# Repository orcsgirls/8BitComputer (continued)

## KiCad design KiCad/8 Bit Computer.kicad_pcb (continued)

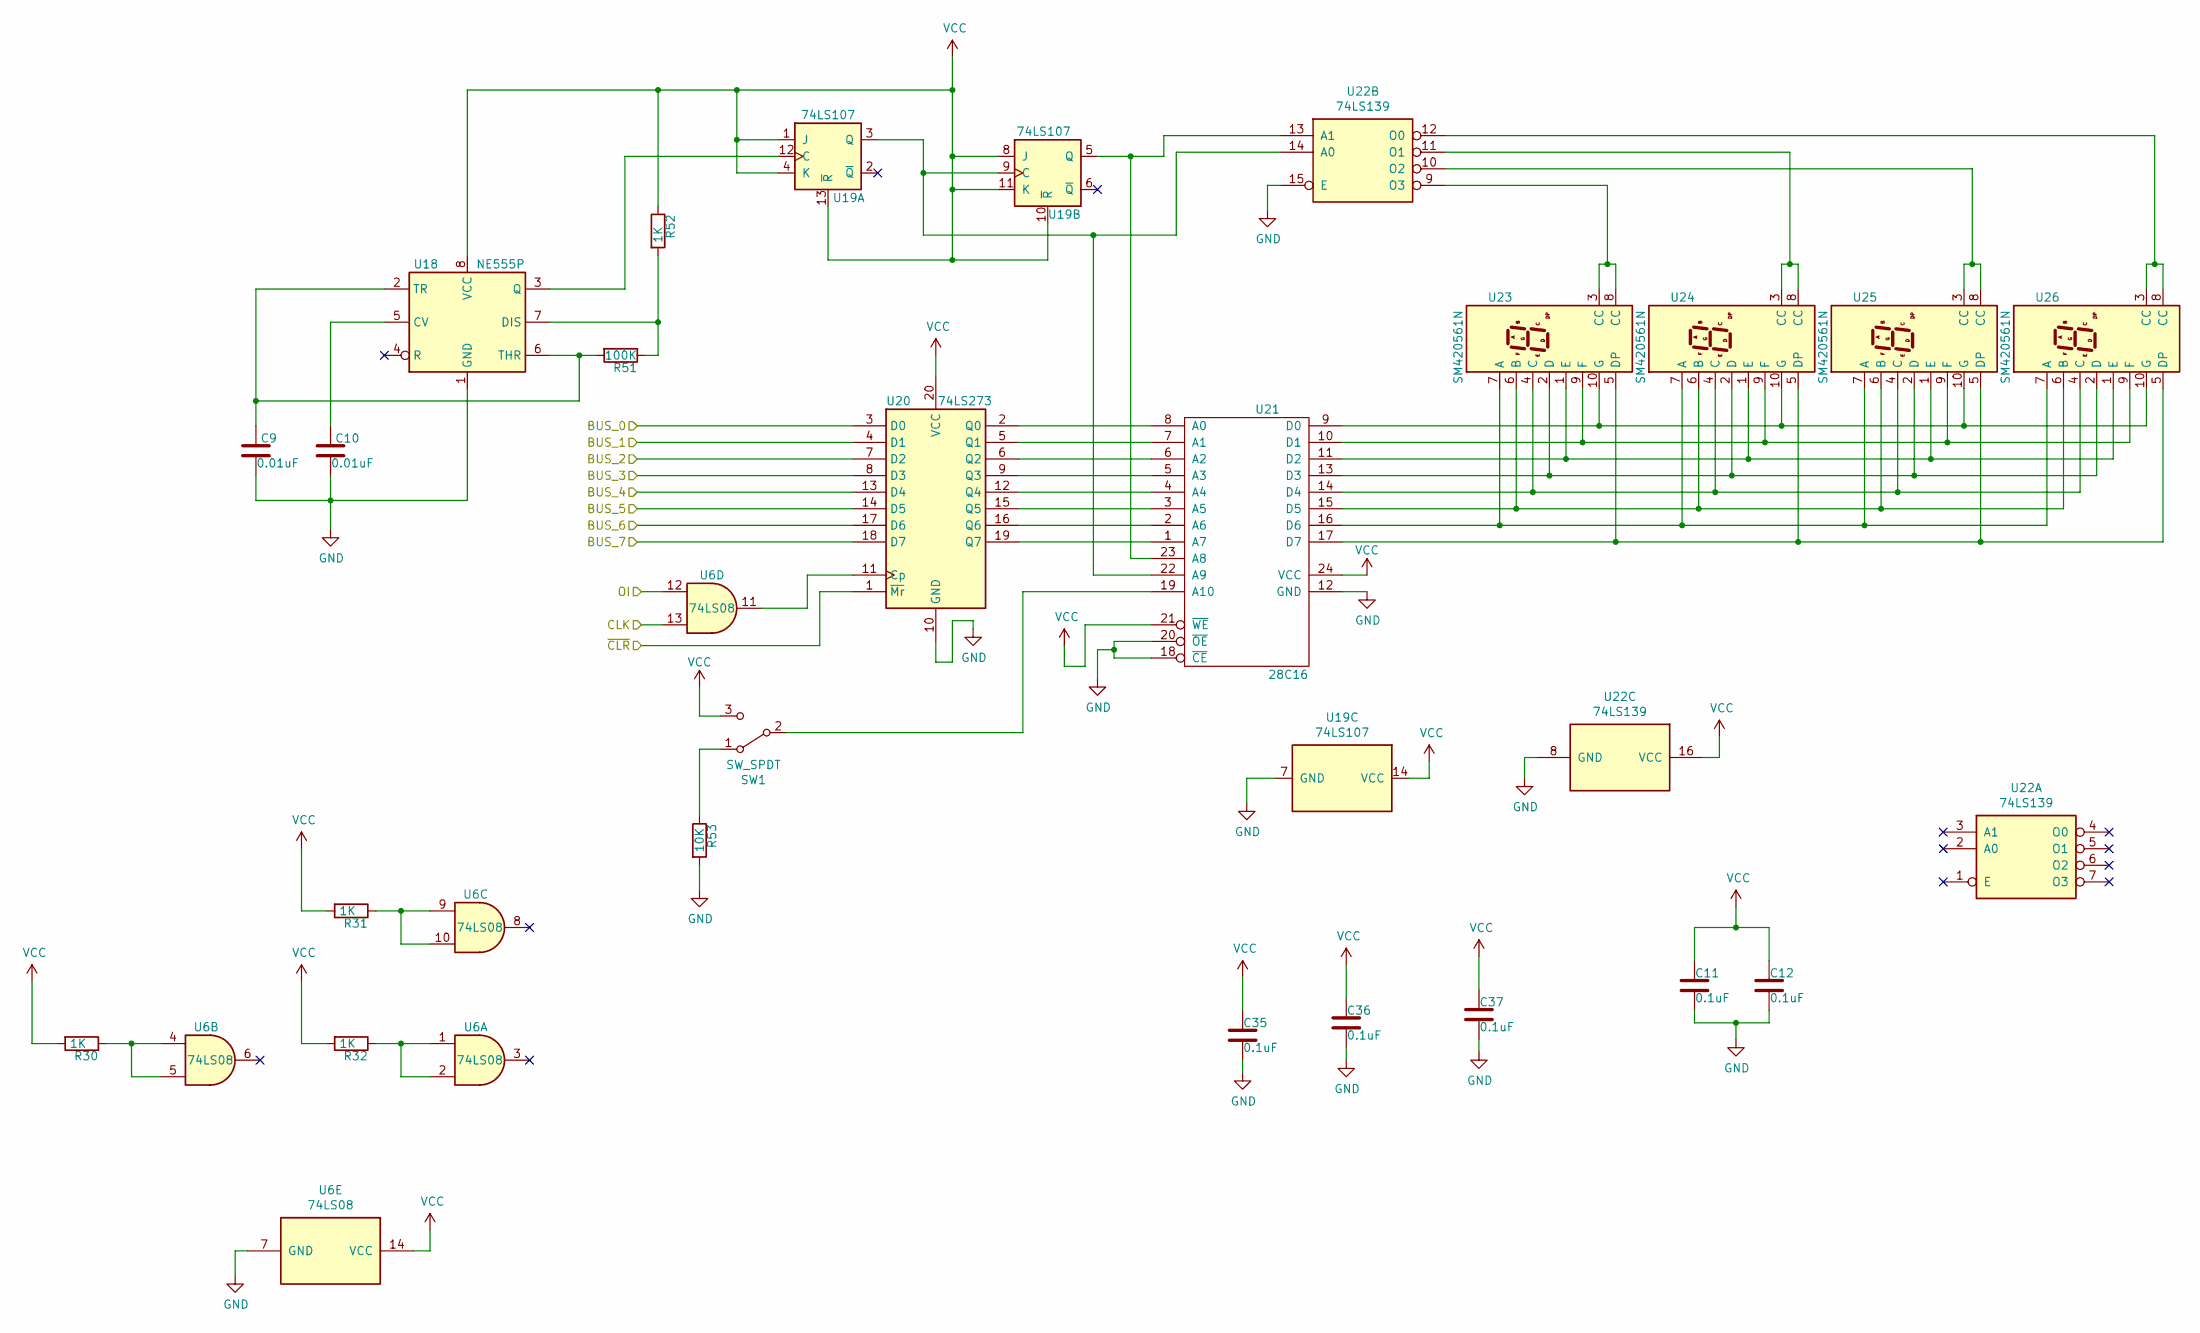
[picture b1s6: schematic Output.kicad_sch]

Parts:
C9, C10: 0.01uF; C_Disc_D4.3mm_W1.9mm_P5.00mm
C11, C12, C35, C36, C37: 0.1uF; C_Disc_D4.3mm_W1.9mm_P5.00mm
R30, R31, R32, R52: 1K; R_Axial_DIN0207_L6.3mm_D2.5mm_P7.62mm_Horizontal
R51: 100K; R_Axial_DIN0207_L6.3mm_D2.5mm_P7.62mm_Horizontal
R53: 10K; R_Axial_DIN0207_L6.3mm_D2.5mm_P7.62mm_Horizontal
SW1: SW_SPDT; SW_Slide_1P2T_CK_OS102011MS2Q
U6: 74LS08; DIP-14_W7.62mm_Socket_LongPads
U18: NE555P; DIP-8_W7.62mm_Socket_LongPads
U19: 74LS107; DIP-14_W7.62mm_Socket_LongPads
U20: 74LS273; DIP-20_W7.62mm_Socket_LongPads
U21: 28C16; DIP-24_W15.24mm_Socket_LongPads
U22: 74LS139; DIP-16_W7.62mm_Socket_LongPads
U23, U24, U25, U26: SM420561N; 7SegmentLED_LTS6760_LTS6780

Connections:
/ALU/BUS_0: U20.3 (D0); also elsewhere on the board
/ALU/BUS_1: U20.4 (D1); also elsewhere on the board
/ALU/BUS_2: U20.7 (D2); also elsewhere on the board
/ALU/BUS_3: U20.8 (D3); also elsewhere on the board
/ALU/BUS_4: U20.13 (D4); also elsewhere on the board
/ALU/BUS_5: U20.14 (D5); also elsewhere on the board
/ALU/BUS_6: U20.17 (D6); also elsewhere on the board
/ALU/BUS_7: U20.18 (D7); also elsewhere on the board
/ALU/CLK: U6.13; also elsewhere on the board
/Arduino_Interface/~CLR: U20.1 (~Mr); also elsewhere on the board
/Control_Logic/OI: U6.12; also elsewhere on the board
GND: C9.2, C10.2, C11.2, C12.2, C35.2, C36.2, C37.2, R53.2, U6.7 (GND), U18.1 (GND), U19.7 (GND), U20.10 (GND), U21.12 (GND), U21.18 (~CE), U21.20 (~OE), U22.8 (GND), U22.15 (E); also elsewhere on the board
unnamed: R30.1, U6.4, U6.5
unnamed: R31.1, U6.9, U6.10
unnamed: R32.1, U6.1, U6.2
unnamed: R53.1, SW1.1 (A)
unnamed: SW1.2 (B), U21.19 (A10)
unnamed: C10.1, U18.5 (CV)
unnamed: R51.1, R52.2, U18.7 (DIS)
unnamed: U18.3 (Q), U19.12 (C)
unnamed: C9.1, R51.2, U18.2 (TR), U18.6 (THR)
unnamed: U19.3 (Q), U19.9 (C), U21.22 (A9), U22.14 (A0)
unnamed: U19.5 (Q), U21.23 (A8), U22.13 (A1)
unnamed: U6.11, U20.11 (Cp)
unnamed: U20.2 (Q0), U21.8 (A0)
unnamed: U20.5 (Q1), U21.7 (A1)
unnamed: U20.6 (Q2), U21.6 (A2)
unnamed: U20.9 (Q3), U21.5 (A3)
unnamed: U20.12 (Q4), U21.4 (A4)
unnamed: U20.15 (Q5), U21.3 (A5)
unnamed: U20.16 (Q6), U21.2 (A6)
unnamed: U20.19 (Q7), U21.1 (A7)
unnamed: U21.9 (D0), U23.10 (G), U24.10 (G), U25.10 (G), U26.10 (G)
unnamed: U21.10 (D1), U23.9 (F), U24.9 (F), U25.9 (F), U26.9 (F)
unnamed: U21.11 (D2), U23.1 (E), U24.1 (E), U25.1 (E), U26.1 (E)
unnamed: U21.13 (D3), U23.2 (D), U24.2 (D), U25.2 (D), U26.2 (D)
unnamed: U21.14 (D4), U23.4 (C), U24.4 (C), U25.4 (C), U26.4 (C)
unnamed: U21.15 (D5), U23.6 (B), U24.6 (B), U25.6 (B), U26.6 (B)
unnamed: U21.16 (D6), U23.7 (A), U24.7 (A), U25.7 (A), U26.7 (A)
unnamed: U21.17 (D7), U23.5 (DP), U24.5 (DP), U25.5 (DP), U26.5 (DP)
unnamed: U22.12 (O0), U26.3 (CC), U26.8 (CC)
unnamed: U22.11 (O1), U24.3 (CC), U24.8 (CC)
unnamed: U22.10 (O2), U25.3 (CC), U25.8 (CC)
unnamed: U22.9 (O3), U23.3 (CC), U23.8 (CC)
VCC: C11.1, C12.1, C35.1, C36.1, C37.1, R30.2, R31.2, R32.2, R52.1, SW1.3 (C), U6.14 (VCC), U18.8 (VCC), U19.1 (J), U19.4 (K), U19.8 (J), U19.10 (~R), U19.11 (K), U19.13 (~R), U19.14 (VCC), U20.20 (VCC), U21.21 (~WE), U21.24 (VCC), U22.16 (VCC); also elsewhere on the board

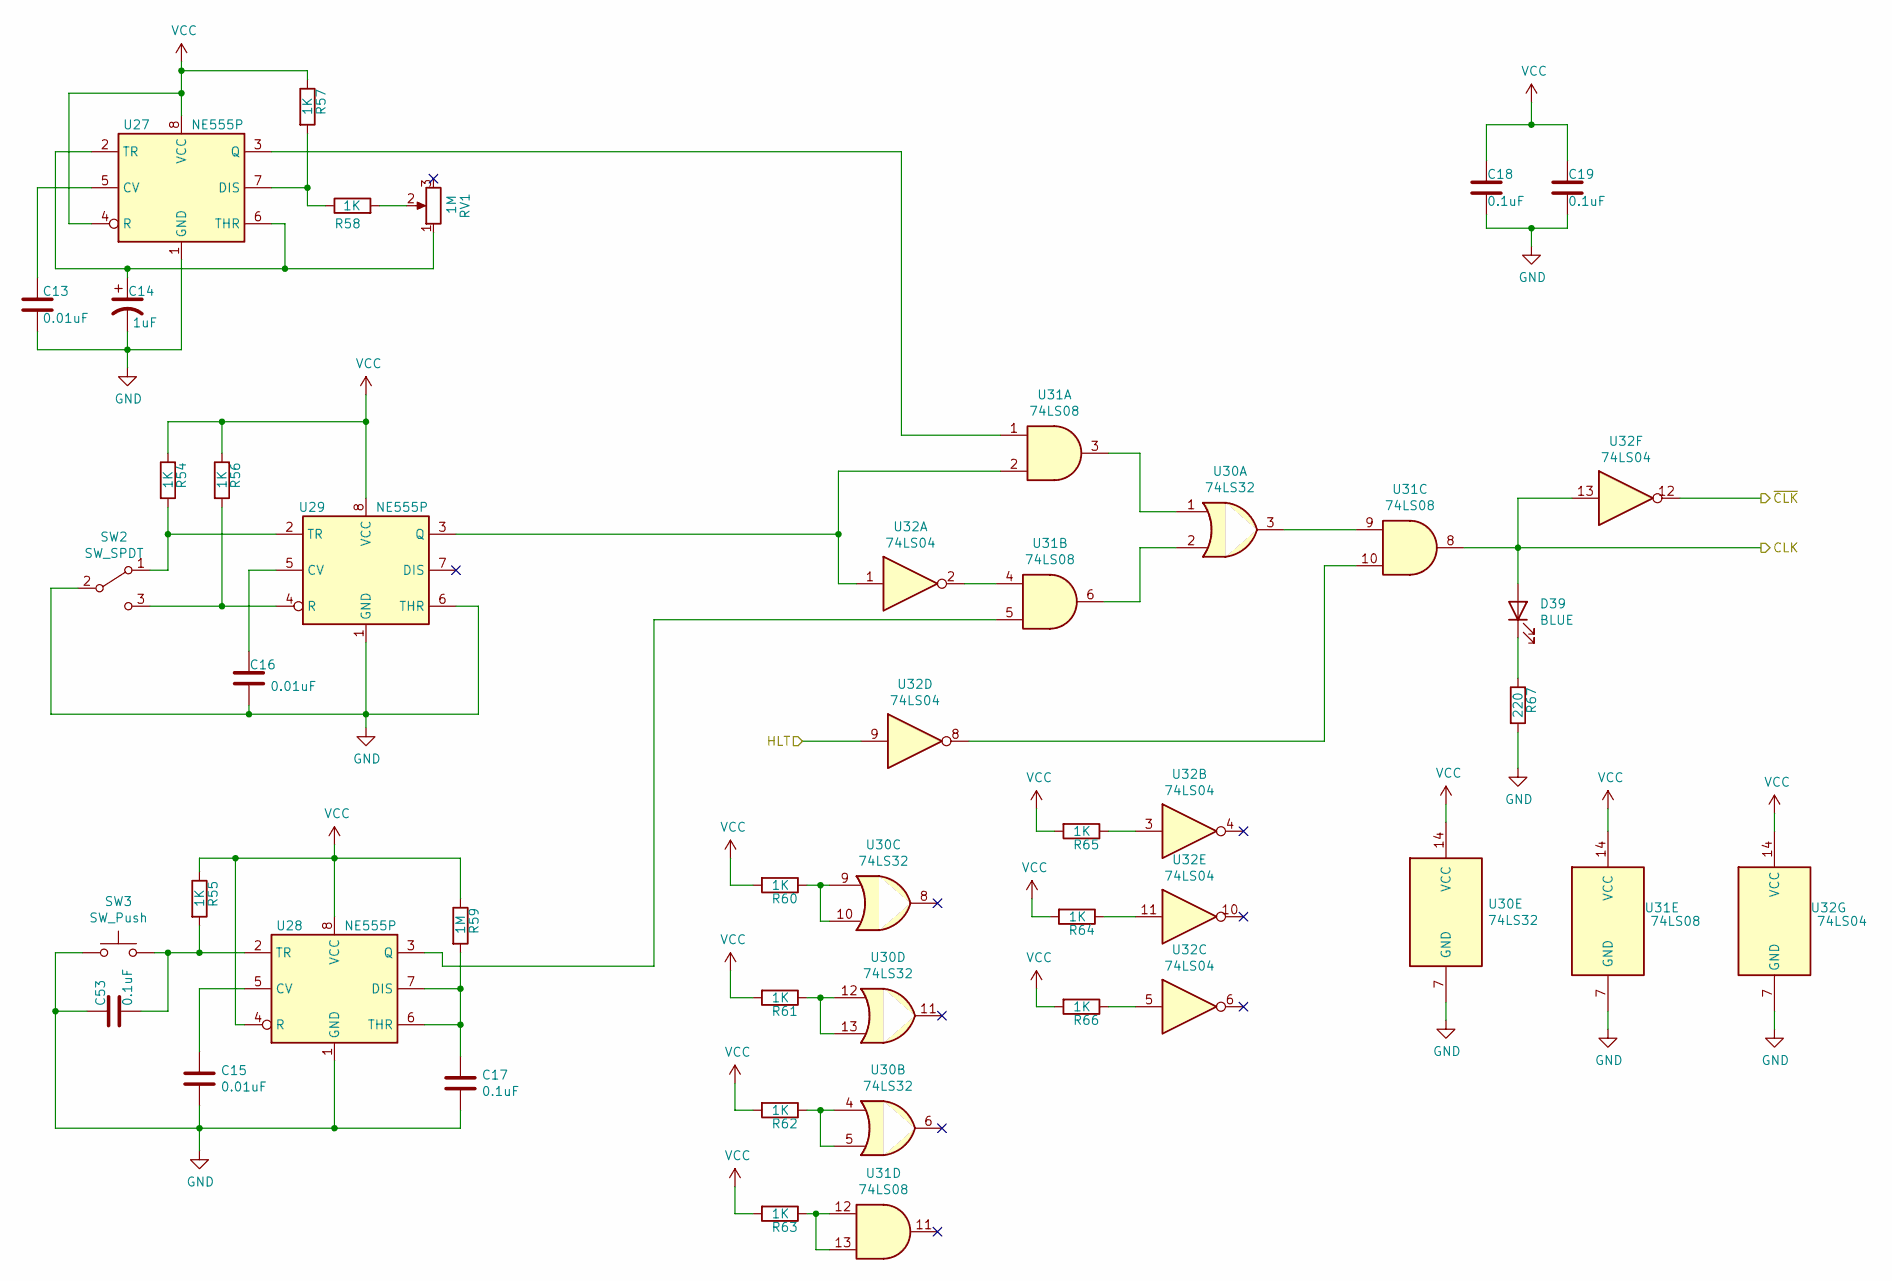
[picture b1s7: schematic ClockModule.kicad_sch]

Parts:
C13, C15, C16: 0.01uF; C_Disc_D4.3mm_W1.9mm_P5.00mm
C14: 1uF; CP_Radial_D5.0mm_P2.00mm
C17, C18, C19, C53: 0.1uF; C_Disc_D4.3mm_W1.9mm_P5.00mm
D39: BLUE; LED_D5.0mm
R54, R55, R56, R57, R58, R60, R61, R62, R63, R64, R65, R66: 1K; R_Axial_DIN0207_L6.3mm_D2.5mm_P7.62mm_Horizontal
R59: 1M; R_Axial_DIN0207_L6.3mm_D2.5mm_P7.62mm_Horizontal
R67: 220; R_Axial_DIN0207_L6.3mm_D2.5mm_P7.62mm_Horizontal
RV1: 1M; Potentiometer-5.5mm
SW2: SW_SPDT; SW_Slide_1P2T_CK_OS102011MS2Q
SW3: SW_Push; SW_PUSH_6mm_H5mm
U27, U28, U29: NE555P; DIP-8_W7.62mm
U30: 74LS32; DIP-14_W7.62mm_Socket_LongPads
U31: 74LS08; DIP-14_W7.62mm_Socket_LongPads
U32: 74LS04; DIP-14_W7.62mm_Socket_LongPads

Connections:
/ALU/CLK: D39.2 (A), U31.8, U32.13; also elsewhere on the board
/ClockModule/HLT: U32.9; also elsewhere on the board
/ClockModule/~CLK: U32.12; also elsewhere on the board
GND: C13.2, C14.2, C15.2, C16.2, C17.2, C18.2, C19.2, C53.1, R67.2, SW2.2 (B), SW3.1, U27.1 (GND), U28.1 (GND), U29.1 (GND), U29.6 (THR), U30.7 (GND), U31.7 (GND), U32.7 (GND); also elsewhere on the board
unnamed: D39.1 (K), R67.1
unnamed: R58.2, RV1.2
unnamed: R60.1, U30.9, U30.10
unnamed: R61.1, U30.12, U30.13
unnamed: R62.1, U30.4, U30.5
unnamed: R63.1, U31.12, U31.13
unnamed: R64.1, U32.11
unnamed: R65.1, U32.3
unnamed: R66.1, U32.5
unnamed: R54.2, SW2.1 (A), U29.2 (TR)
unnamed: R56.2, SW2.3 (C), U29.4 (R)
unnamed: C13.1, U27.5 (CV)
unnamed: R57.2, R58.1, U27.7 (DIS)
unnamed: U27.3 (Q), U31.1
unnamed: C14.1, RV1.1, U27.2 (TR), U27.6 (THR)
unnamed: C15.1, U28.5 (CV)
unnamed: C17.1, R59.2, U28.6 (THR), U28.7 (DIS)
unnamed: U28.3 (Q), U31.5
unnamed: C53.2, R55.2, SW3.2, U28.2 (TR)
unnamed: C16.1, U29.5 (CV)
unnamed: U29.3 (Q), U31.2, U32.1
unnamed: U30.1, U31.3
unnamed: U30.2, U31.6
unnamed: U30.3, U31.9
unnamed: U31.4, U32.2
unnamed: U31.10, U32.8
VCC: C18.1, C19.1, R54.1, R55.1, R56.1, R57.1, R59.1, R60.2, R61.2, R62.2, R63.2, R64.2, R65.2, R66.2, U27.4 (R), U27.8 (VCC), U28.4 (R), U28.8 (VCC), U29.8 (VCC), U30.14 (VCC), U31.14 (VCC), U32.14 (VCC); also elsewhere on the board

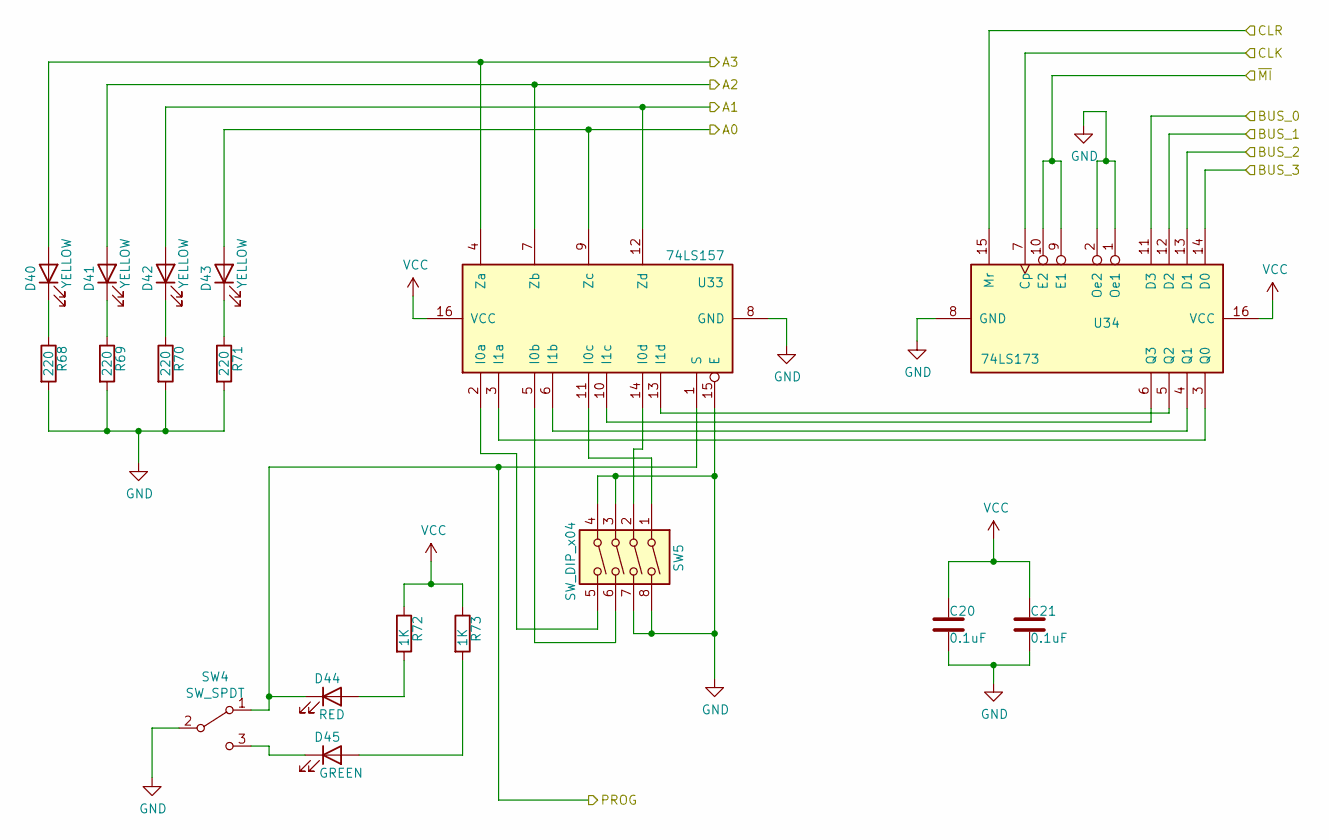
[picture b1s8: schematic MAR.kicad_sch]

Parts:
C20, C21: 0.1uF; C_Disc_D4.3mm_W1.9mm_P5.00mm
D40, D41, D42, D43: YELLOW; LED_D5.0mm
D44: RED; LED_D5.0mm
D45: GREEN; LED_D5.0mm
R68, R69, R70, R71: 220; R_Axial_DIN0207_L6.3mm_D2.5mm_P7.62mm_Horizontal
R72, R73: 1K; R_Axial_DIN0207_L6.3mm_D2.5mm_P7.62mm_Horizontal
SW4: SW_SPDT; SW_Slide_1P2T_CK_OS102011MS2Q
SW5: SW_DIP_x04; SW_DIP_SPSTx04_Slide_9.78x12.34mm_W7.62mm_P2.54mm
U33: 74LS157; DIP-16_W7.62mm_Socket_LongPads
U34: 74LS173; DIP-16_W7.62mm_Socket_LongPads

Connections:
/ALU/BUS_0: U34.11 (D3); also elsewhere on the board
/ALU/BUS_1: U34.12 (D2); also elsewhere on the board
/ALU/BUS_2: U34.13 (D1); also elsewhere on the board
/ALU/BUS_3: U34.14 (D0); also elsewhere on the board
/ALU/CLK: U34.7 (Cp); also elsewhere on the board
/ALU/CLR: U34.15 (Mr); also elsewhere on the board
/Control_Logic/~MI: U34.9 (E1), U34.10 (E2); also elsewhere on the board
/MAR/A0: D43.2 (A), U33.9 (Zc); also elsewhere on the board
/MAR/A1: D42.2 (A), U33.12 (Zd); also elsewhere on the board
/MAR/A2: D41.2 (A), U33.7 (Zb); also elsewhere on the board
/MAR/A3: D40.2 (A), U33.4 (Za); also elsewhere on the board
/MAR/PROG: D44.1 (K), SW4.1 (A), U33.1 (S); also elsewhere on the board
GND: C20.2, C21.2, R68.2, R69.2, R70.2, R71.2, SW4.2 (B), SW5.3, SW5.4, SW5.7, SW5.8, U33.8 (GND), U33.15 (E), U34.1 (Oe1), U34.2 (Oe2), U34.8 (GND); also elsewhere on the board
unnamed: D40.1 (K), R68.1
unnamed: D41.1 (K), R69.1
unnamed: D42.1 (K), R70.1
unnamed: D43.1 (K), R71.1
unnamed: D44.2 (A), R72.2
unnamed: D45.2 (A), R73.2
unnamed: D45.1 (K), SW4.3 (C)
unnamed: SW5.5, U33.2 (I0a)
unnamed: SW5.6, U33.5 (I0b)
unnamed: SW5.1, U33.11 (I0c)
unnamed: SW5.2, U33.14 (I0d)
unnamed: U33.3 (I1a), U34.3 (Q0)
unnamed: U33.6 (I1b), U34.4 (Q1)
unnamed: U33.10 (I1c), U34.6 (Q3)
unnamed: U33.13 (I1d), U34.5 (Q2)
VCC: C20.1, C21.1, R72.1, R73.1, U33.16 (VCC), U34.16 (VCC); also elsewhere on the board

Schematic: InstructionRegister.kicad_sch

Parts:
C38, C39, C40: 0.1uF; C_Disc_D4.3mm_W1.9mm_P5.00mm
D46, D47, D48, D49: BLUE; LED_D5.0mm
D50, D51, D52, D53: YELLOW; LED_D5.0mm
R74, R75, R76, R77, R78, R79, R80, R81: 220; R_Axial_DIN0207_L6.3mm_D2.5mm_P7.62mm_Horizontal
U35: 74LS245; DIP-20_W7.62mm_Socket_LongPads
U36, U37: 74LS173; DIP-16_W7.62mm_Socket_LongPads

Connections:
/ALU/BUS_0: U35.11 (B7), U37.11 (D3); also elsewhere on the board
/ALU/BUS_1: U35.12 (B6), U37.12 (D2); also elsewhere on the board
/ALU/BUS_2: U35.13 (B5), U37.13 (D1); also elsewhere on the board
/ALU/BUS_3: U35.14 (B4), U37.14 (D0); also elsewhere on the board
/ALU/BUS_4: U35.15 (B3), U36.11 (D3); also elsewhere on the board
/ALU/BUS_5: U35.16 (B2), U36.12 (D2); also elsewhere on the board
/ALU/BUS_6: U35.17 (B1), U36.13 (D1); also elsewhere on the board
/ALU/BUS_7: U35.18 (B0), U36.14 (D0); also elsewhere on the board
/ALU/CLK: U36.7 (Cp), U37.7 (Cp); also elsewhere on the board
/ALU/CLR: U36.15 (Mr), U37.15 (Mr); also elsewhere on the board
/Control_Logic/IR_4: D49.2 (A), U36.6 (Q3); also elsewhere on the board
/Control_Logic/IR_5: D48.2 (A), U36.5 (Q2); also elsewhere on the board
/Control_Logic/IR_6: D47.2 (A), U36.4 (Q1); also elsewhere on the board
/Control_Logic/IR_7: D46.2 (A), U36.3 (Q0); also elsewhere on the board
/Control_Logic/~II: U36.9 (E1), U36.10 (E2), U37.9 (E1), U37.10 (E2); also elsewhere on the board
/Control_Logic/~IO: U35.19 (CE); also elsewhere on the board
GND: C38.2, C39.2, C40.2, R74.2, R75.2, R76.2, R77.2, R78.2, R79.2, R80.2, R81.2, U35.2 (A0), U35.3 (A1), U35.4 (A2), U35.5 (A3), U35.10 (GND), U36.1 (Oe1), U36.2 (Oe2), U36.8 (GND), U37.1 (Oe1), U37.2 (Oe2), U37.8 (GND); also elsewhere on the board
unnamed: D46.1 (K), R74.1
unnamed: D47.1 (K), R75.1
unnamed: D48.1 (K), R76.1
unnamed: D49.1 (K), R77.1
unnamed: D50.2 (A), U35.6 (A4), U37.3 (Q0)
unnamed: D50.1 (K), R78.1
unnamed: D51.2 (A), U35.7 (A5), U37.4 (Q1)
unnamed: D51.1 (K), R79.1
unnamed: D52.2 (A), U35.8 (A6), U37.5 (Q2)
unnamed: D52.1 (K), R80.1
unnamed: D53.2 (A), U35.9 (A7), U37.6 (Q3)
unnamed: D53.1 (K), R81.1
VCC: C38.1, C39.1, C40.1, U35.1 (A->B), U35.20 (VCC), U36.16 (VCC), U37.16 (VCC); also elsewhere on the board

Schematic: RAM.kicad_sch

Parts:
C24: 0.01uF; C_Disc_D4.3mm_W1.9mm_P5.00mm
C25, C26, C41, C42, C43, C44, C45, C46, C47: 0.1uF; C_Disc_D4.3mm_W1.9mm_P5.00mm
D54, D55, D56, D57, D58, D59, D60, D61: RED; LED_D5.0mm
R82, R83, R84, R85, R86, R87, R88, R89: 220; R_Axial_DIN0207_L6.3mm_D2.5mm_P7.62mm_Horizontal
R90: 1K; R_Axial_DIN0207_L6.3mm_D2.5mm_P7.62mm_Horizontal
SW6: SW_Push; SW_PUSH_6mm_H5mm
SW7: SW_DIP_x08; SW_DIP_SPSTx08_Slide_9.78x22.5mm_W7.62mm_P2.54mm
U38, U39: 74LS04; DIP-14_W7.62mm_Socket_LongPads
U40, U45, U46: 74LS157; DIP-16_W7.62mm_Socket_LongPads
U41, U44: 74189; DIP-16_W7.62mm_Socket_LongPads
U42: 74LS00; DIP-14_W7.62mm_Socket_LongPads
U43: 74LS245; DIP-20_W7.62mm_Socket_LongPads

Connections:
/ALU/BUS_0: U43.11 (B7), U46.10 (I1c); also elsewhere on the board
/ALU/BUS_1: U43.12 (B6), U46.13 (I1d); also elsewhere on the board
/ALU/BUS_2: U43.13 (B5), U46.6 (I1b); also elsewhere on the board
/ALU/BUS_3: U43.14 (B4), U46.3 (I1a); also elsewhere on the board
/ALU/BUS_4: U43.15 (B3), U45.10 (I1c); also elsewhere on the board
/ALU/BUS_5: U43.16 (B2), U45.13 (I1d); also elsewhere on the board
/ALU/BUS_6: U43.17 (B1), U45.6 (I1b); also elsewhere on the board
/ALU/BUS_7: U43.18 (B0), U45.3 (I1a); also elsewhere on the board
/ALU/CLK: U39.9; also elsewhere on the board
/Arduino_Interface/RI: U42.2; also elsewhere on the board
/Control_Logic/~RO: U43.19 (CE); also elsewhere on the board
/MAR/A0: U41.1 (A0), U44.1 (A0); also elsewhere on the board
/MAR/A1: U41.15 (A1), U44.15 (A1); also elsewhere on the board
/MAR/A2: U41.14 (A2), U44.14 (A2); also elsewhere on the board
/MAR/A3: U41.13 (A3), U44.13 (A3); also elsewhere on the board
/MAR/PROG: U40.1 (S), U45.1 (S), U46.1 (S); also elsewhere on the board
GND: C25.2, C26.2, C41.2, C42.2, C43.2, C44.2, C45.2, C46.2, C47.2, R82.2, R83.2, R84.2, R85.2, R86.2, R87.2, R88.2, R89.2, R90.1, SW6.1, SW7.3, SW7.4, SW7.7, SW7.8, SW7.11, SW7.12, SW7.15, SW7.16, U38.7 (GND), U38.11, U38.13, U39.7 (GND), U40.8 (GND), U40.15 (E), U41.2 (~CS), U41.8 (GND), U42.4, U42.5, U42.7 (GND), U42.9, U42.10, U42.12, U42.13, U43.10 (GND), U44.2 (~CS), U44.8 (GND), U45.8 (GND), U45.15 (E), U46.8 (GND), U46.15 (E); also elsewhere on the board
unnamed: C24.1, U39.10
unnamed: C24.2, R90.2, U42.1
unnamed: D54.2 (A), U38.2, U43.2 (A0)
unnamed: D54.1 (K), R82.1
unnamed: D55.2 (A), U38.4, U43.3 (A1)
unnamed: D55.1 (K), R83.1
unnamed: D56.2 (A), U38.6, U43.4 (A2)
unnamed: D56.1 (K), R84.1
unnamed: D57.2 (A), U38.8, U43.5 (A3)
unnamed: D57.1 (K), R85.1
unnamed: D58.2 (A), U39.12, U43.6 (A4)
unnamed: D58.1 (K), R86.1
unnamed: D59.2 (A), U39.2, U43.7 (A5)
unnamed: D59.1 (K), R87.1
unnamed: D60.2 (A), U39.4, U43.8 (A6)
unnamed: D60.1 (K), R88.1
unnamed: D61.2 (A), U39.6, U43.9 (A7)
unnamed: D61.1 (K), R89.1
unnamed: U39.8, U39.11
unnamed: SW6.2, U40.14 (I0d)
unnamed: U40.13 (I1d), U42.3
unnamed: U40.12 (Zd), U41.3 (~WE), U44.3 (~WE)
unnamed: U41.4 (D1), U45.4 (Za)
unnamed: U41.6 (D2), U45.7 (Zb)
unnamed: U41.10 (D3), U45.12 (Zd)
unnamed: U41.12 (D4), U45.9 (Zc)
unnamed: U38.1, U41.5 (~O1)
unnamed: U38.3, U41.7 (~O2)
unnamed: U38.5, U41.9 (~O3)
unnamed: U38.9, U41.11 (~O4)
unnamed: U44.4 (D1), U46.9 (Zc)
unnamed: U44.6 (D2), U46.12 (Zd)
unnamed: U44.10 (D3), U46.7 (Zb)
unnamed: U44.12 (D4), U46.4 (Za)
unnamed: U39.5, U44.5 (~O1)
unnamed: U39.3, U44.7 (~O2)
unnamed: U39.1, U44.9 (~O3)
unnamed: U39.13, U44.11 (~O4)
unnamed: SW7.9, U45.2 (I0a)
unnamed: SW7.10, U45.5 (I0b)
unnamed: SW7.5, U45.11 (I0c)
unnamed: SW7.6, U45.14 (I0d)
unnamed: SW7.13, U46.2 (I0a)
unnamed: SW7.14, U46.5 (I0b)
unnamed: SW7.1, U46.11 (I0c)
unnamed: SW7.2, U46.14 (I0d)
VCC: C25.1, C26.1, C41.1, C42.1, C43.1, C44.1, C45.1, C46.1, C47.1, U38.14 (VCC), U39.14 (VCC), U40.16 (VCC), U41.16 (VCC), U42.14 (VCC), U43.1 (A->B), U43.20 (VCC), U44.16 (VCC), U45.16 (VCC), U46.16 (VCC); also elsewhere on the board

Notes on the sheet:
Clock buffering (Added TEP)

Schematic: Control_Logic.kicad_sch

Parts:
C27, C28, C48, C49, C50, C51, C52, C100: 0.1uF; C_Disc_D4.3mm_W1.9mm_P5.00mm
D62, D63, D64, D65, D66: GREEN; LED_D5.0mm
D67, D68, D69: RED; LED_D5.0mm
D70, D71, D72, D73, D74, D75, D76, D77, D78, D79, D80, D81, D82, D83, D84, D85: BLUE; LED_D5.0mm
R91: 1K; R_Axial_DIN0207_L6.3mm_D2.5mm_P7.62mm_Horizontal
R92, R93, R94, R95, R96, R97, R98, R99, R100, R101, R102, R103, R104, R105, R106, R107, R108, R109, R110, R111, R112, R113, R114, R115: 220; R_Axial_DIN0207_L6.3mm_D2.5mm_P7.62mm_Horizontal
R300, R301, R302, R303, R304, R305, R306, R307, R308, R310, R312, R313, R314, R315: 3.3k; R_Axial_DIN0207_L6.3mm_D2.5mm_P7.62mm_Horizontal
R309, R311: 1k; R_Axial_DIN0207_L6.3mm_D2.5mm_P7.62mm_Horizontal
SW8: RESET; SW_PUSH_6mm_H5mm
U47, U100: 74LS00; DIP-14_W7.62mm_Socket_LongPads
U48: 74LS161; DIP-16_W7.62mm_Socket_LongPads
U49: 74LS138; DIP-16_W7.62mm_Socket_LongPads
U50, U51: 28C16; DIP-24_W15.24mm_Socket_LongPads
U52, U53: 74LS04; DIP-14_W7.62mm_Socket_LongPads

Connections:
/ALU/CF: U50.23 (A8), U51.23 (A8); also elsewhere on the board
/ALU/CLR: U47.11; also elsewhere on the board
/ALU/SU: D79.2 (A), R309.2, U51.16 (D6); also elsewhere on the board
/ALU/ZF: U50.22 (A9), U51.22 (A9); also elsewhere on the board
/ALU/~EO: U53.2; also elsewhere on the board
/ALU/~FI: U53.6; also elsewhere on the board
/A_Register/~AI: U52.10; also elsewhere on the board
/A_Register/~AO: U52.8; also elsewhere on the board
/Arduino_Interface/MI: D71.2 (A), R301.2, U50.16 (D6), U52.1; also elsewhere on the board
/Arduino_Interface/RI: D72.2 (A), R302.2, U50.15 (D5); also elsewhere on the board
/Arduino_Interface/RO: D73.2 (A), R303.2, U50.14 (D4), U52.3; also elsewhere on the board
/Arduino_Interface/~CE: U50.18 (~CE), U51.18 (~CE), U100.4, U100.5; also elsewhere on the board
/Arduino_Interface/~CLR: U47.4, U47.8, U47.12, U47.13; also elsewhere on the board
/B_Register/~BI: U53.4; also elsewhere on the board
/ClockModule/HLT: D70.2 (A), R300.2, U50.17 (D7); also elsewhere on the board
/ClockModule/~CLK: U48.2 (CP); also elsewhere on the board
/Control_Logic/CE: D82.2 (A), R311.2, U51.13 (D3); also elsewhere on the board
/Control_Logic/IR_4: U50.5 (A3), U51.5 (A3); also elsewhere on the board
/Control_Logic/IR_5: U50.4 (A4), U51.4 (A4); also elsewhere on the board
/Control_Logic/IR_6: U50.3 (A5), U51.3 (A5); also elsewhere on the board
/Control_Logic/IR_7: U50.2 (A6), U51.2 (A6); also elsewhere on the board
/Control_Logic/OI: D81.2 (A), R310.2, U51.14 (D4); also elsewhere on the board
/Control_Logic/~CO: U53.12; also elsewhere on the board
/Control_Logic/~II: U52.12; also elsewhere on the board
/Control_Logic/~IO: U52.6; also elsewhere on the board
/Control_Logic/~J: U53.10; also elsewhere on the board
/Control_Logic/~MI: U52.2; also elsewhere on the board
/Control_Logic/~RO: U52.4; also elsewhere on the board
GND: C27.2, C28.2, C48.2, C49.2, C50.2, C51.2, C52.2, C100.2, R91.1, R97.2, R98.2, R99.2, R100.2, R101.2, R102.2, R103.2, R104.2, R105.2, R106.2, R107.2, R108.2, R109.2, R110.2, R111.2, R112.2, R113.2, R114.2, R115.2, R300.1, R301.1, R302.1, R303.1, R304.1, R305.1, R306.1, R307.1, R308.1, R309.1, R310.1, R311.1, R312.1, R313.1, R314.1, R315.1, U47.7 (GND), U48.8 (GND), U49.4 (E1), U49.5 (E2), U49.8 (GND), U50.1 (A7), U50.12 (GND), U50.19 (A10), U50.20 (~OE), U51.12 (GND), U51.19 (A10), U51.20 (~OE), U52.7 (GND), U53.7 (GND), U53.9, U100.7 (GND), U100.12, U100.13; also elsewhere on the board
unnamed: D62.2 (A), R92.2
unnamed: D62.1 (K), U49.11 (O4)
unnamed: D63.2 (A), R93.2
unnamed: D63.1 (K), U49.12 (O3)
unnamed: D64.2 (A), R94.2
unnamed: D64.1 (K), U49.13 (O2)
unnamed: D65.2 (A), R95.2
unnamed: D65.1 (K), U49.14 (O1)
unnamed: D66.2 (A), R96.2
unnamed: D66.1 (K), U49.15 (O0)
unnamed: D67.2 (A), U48.14 (Q0), U49.1 (A0), U50.8 (A0), U51.8 (A0)
unnamed: D67.1 (K), R97.1
unnamed: D68.2 (A), U48.13 (Q1), U49.2 (A1), U50.7 (A1), U51.7 (A1)
unnamed: D68.1 (K), R98.1
unnamed: D69.2 (A), U48.12 (Q2), U49.3 (A2), U50.6 (A2), U51.6 (A2)
unnamed: D69.1 (K), R99.1
unnamed: D70.1 (K), R100.1
unnamed: D71.1 (K), R101.1
unnamed: D72.1 (K), R102.1
unnamed: D73.1 (K), R103.1
unnamed: D74.2 (A), R304.2, U50.13 (D3), U52.5
unnamed: D74.1 (K), R104.1
unnamed: D75.2 (A), R305.2, U50.11 (D2), U52.13
unnamed: D75.1 (K), R105.1
unnamed: D76.2 (A), R306.2, U50.10 (D1), U52.11
unnamed: D76.1 (K), R106.1
unnamed: D77.2 (A), R307.2, U50.9 (D0), U52.9
unnamed: D77.1 (K), R107.1
unnamed: D78.2 (A), R308.2, U51.17 (D7), U53.1
unnamed: D78.1 (K), R108.1
unnamed: D79.1 (K), R109.1
unnamed: D80.2 (A), R315.2, U51.15 (D5), U53.3
unnamed: D80.1 (K), R110.1
unnamed: D81.1 (K), R111.1
unnamed: D82.1 (K), R112.1
unnamed: D83.2 (A), R312.2, U51.11 (D2), U53.13
unnamed: D83.1 (K), R113.1
unnamed: D84.2 (A), R313.2, U51.10 (D1), U53.11
unnamed: D84.1 (K), R114.1
unnamed: D85.2 (A), R314.2, U51.9 (D0), U53.5
unnamed: D85.1 (K), R115.1
unnamed: R91.2, SW8.1, U47.9, U47.10
unnamed: U47.1, U47.2, U47.6
unnamed: U48.1 (~MR), U100.8
unnamed: U47.5, U49.10 (O5)
unnamed: U100.1, U100.6
unnamed: U47.3, U100.2
unnamed: U100.3, U100.9, U100.10
VCC: C27.1, C28.1, C48.1, C49.1, C50.1, C51.1, C52.1, C100.1, R92.1, R93.1, R94.1, R95.1, R96.1, SW8.2, U47.14 (VCC), U48.7 (CEP), U48.9 (~PE), U48.10 (CET), U48.16 (VCC), U49.6 (E3), U49.16 (VCC), U50.21 (~WE), U50.24 (VCC), U51.1 (A7), U51.21 (~WE), U51.24 (VCC), U52.14 (VCC), U53.14 (VCC), U100.14 (VCC); also elsewhere on the board

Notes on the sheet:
Added reset logic for Arduino
EEPROMS need pull up resistors for Arduino mod.

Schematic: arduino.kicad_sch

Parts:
A1: Arduino_Nano_v3.x; Arduino_Nano
D600: BLUE; LED_D5.0mm
R600: 220; R_Axial_DIN0207_L6.3mm_D2.5mm_P7.62mm_Horizontal
R601, R602, R603, R605, R609: 10k; R_Axial_DIN0207_L6.3mm_D2.5mm_P7.62mm_Horizontal
R604: 5.1k; R_Axial_DIN0207_L6.3mm_D2.5mm_P7.62mm_Horizontal
R606: 22k; R_Axial_DIN0207_L6.3mm_D2.5mm_P7.62mm_Horizontal
R607: 47k; R_Axial_DIN0207_L6.3mm_D2.5mm_P7.62mm_Horizontal
R608: 100k; R_Axial_DIN0207_L6.3mm_D2.5mm_P7.62mm_Horizontal
SW10: SW_DIP_x04; SW_DIP_SPSTx04_Slide_9.78x12.34mm_W7.62mm_P2.54mm
SW11, SW12: SW_Push; SW_PUSH_6mm_H5mm

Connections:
/ALU/BUS_0: A1.5 (D2); also elsewhere on the board
/ALU/BUS_1: A1.6 (D3); also elsewhere on the board
/ALU/BUS_2: A1.7 (D4); also elsewhere on the board
/ALU/BUS_3: A1.8 (D5); also elsewhere on the board
/ALU/BUS_4: A1.9 (D6); also elsewhere on the board
/ALU/BUS_5: A1.10 (D7); also elsewhere on the board
/ALU/BUS_6: A1.11 (D8); also elsewhere on the board
/ALU/BUS_7: A1.12 (D9); also elsewhere on the board
/ALU/CLK: A1.19 (A0); also elsewhere on the board
/Arduino_Interface/MI: A1.15 (D12); also elsewhere on the board
/Arduino_Interface/RI: A1.14 (D11); also elsewhere on the board
/Arduino_Interface/RO: A1.13 (D10); also elsewhere on the board
/Arduino_Interface/~CE: A1.22 (A3), D600.2 (A), R601.2; also elsewhere on the board
/Arduino_Interface/~CLR: A1.3 (~RESET), A1.28 (~RESET); also elsewhere on the board
GND: A1.4 (GND), A1.29 (GND), R600.2, R602.2, R609.2; also elsewhere on the board
unnamed: A1.20 (A1), R602.1, SW11.1, SW12.1
unnamed: A1.21 (A2), R609.1, SW10.5, SW10.6, SW10.7, SW10.8
unnamed: D600.1 (K), R600.1
unnamed: R603.2, SW11.2
unnamed: R604.2, SW12.2
unnamed: R605.2, SW10.4
unnamed: R606.2, SW10.3
unnamed: R607.2, SW10.2
unnamed: R608.2, SW10.1
VCC: A1.27 (+5V), R601.1, R603.1, R604.1, R605.1, R606.1, R607.1, R608.1; also elsewhere on the board

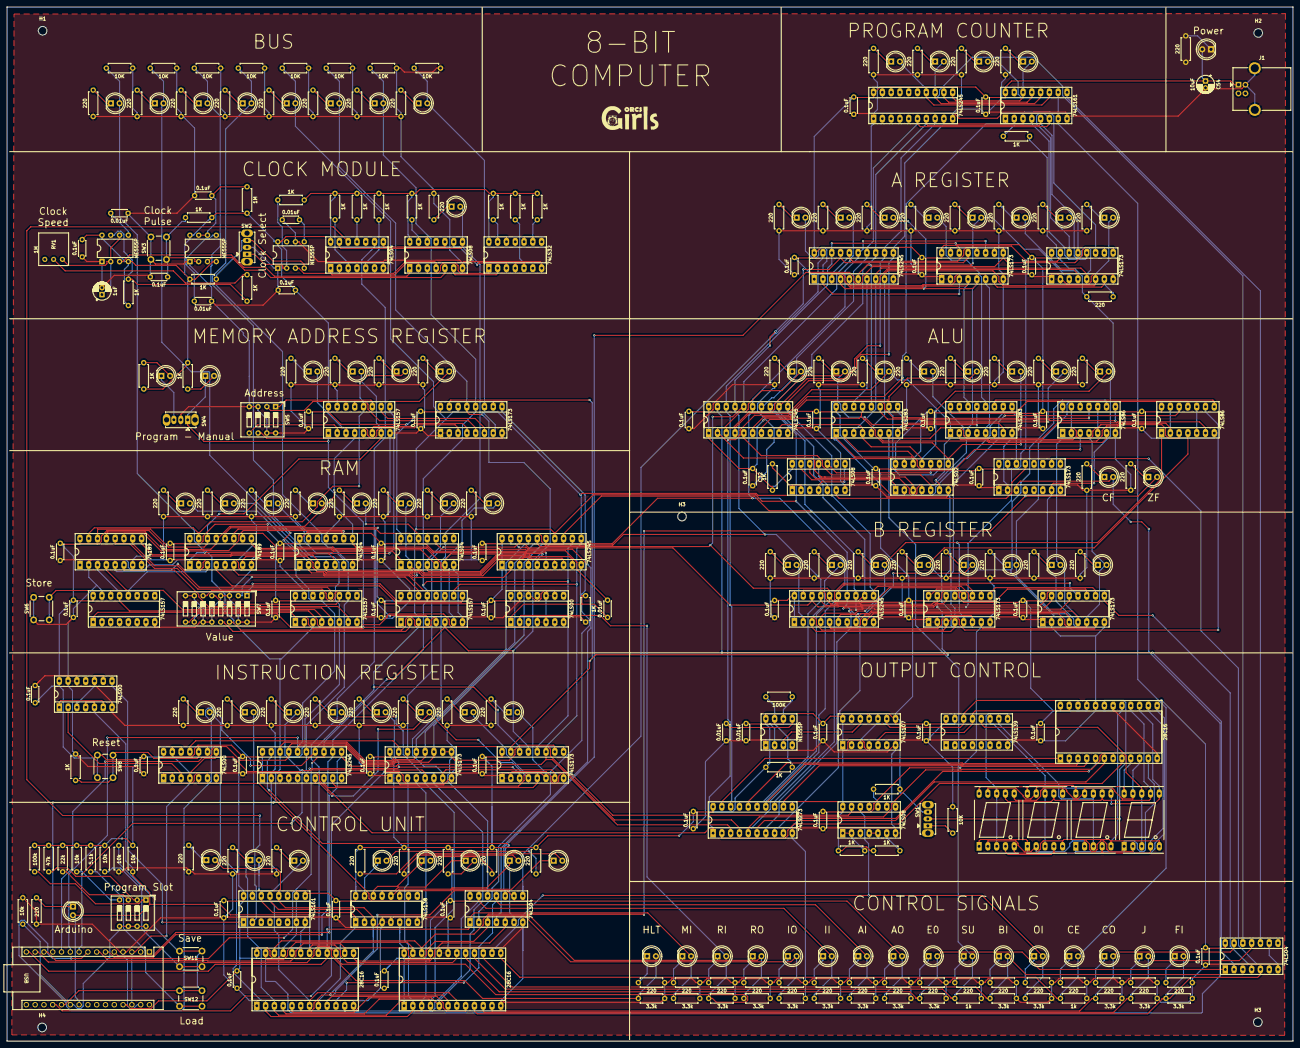
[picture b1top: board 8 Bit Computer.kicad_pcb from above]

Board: 2 copper layers, 371.5 x 298.7 mm, 360 parts (0 on the bottom side), 319 nets.

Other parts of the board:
G99: LOGO
H1, H2, H3, H3#2, H4: MountingHole_2.5mm

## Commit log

2024-08-04 Some fixes and added instruction set help
2024-08-11 Added more instructions
2024-08-16 PCB fixes
    Added missing labels and middle hole
2024-08-18 Fixed Label issue
2024-08-18 Added Power LED
2024-09-02 Bug with arrays for conditional jump fixed
2024-09-04 Updated op codes for camp
2024-09-07 Fixes
2024-09-07 Update Arduino.ino
    Disabled auto load
